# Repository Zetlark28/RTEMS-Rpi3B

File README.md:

# RTEMS-Rpi3B
Hi,

this repository is used for my thesis on RTEMS with rpi 3B+.

there are 4 directory:
- Notes : notes, sketch for thesis and project
- Guide : guide to install RTEMS on Host computer and create the first program
- Thesis : all files for my thesis
- SW : all source code of RTEMS
- HW : kicad
- Documents : all documents of RTEMS, rpi, kicad ecc.

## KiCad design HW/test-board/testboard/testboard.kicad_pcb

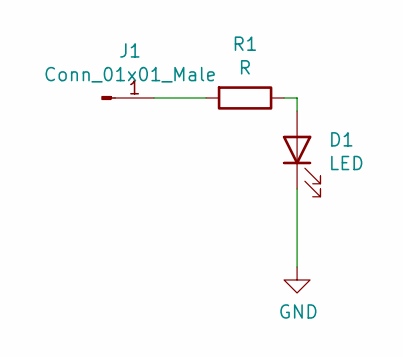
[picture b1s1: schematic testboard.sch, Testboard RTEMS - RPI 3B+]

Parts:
D1: LED; LED_D5.0mm
J1: Conn_01x01_Male; SolderWire-2sqmm_1x01_D2mm_OD3.9mm_Relief2x
R1: R; R_Axial_DIN0204_L3.6mm_D1.6mm_P2.54mm_Vertical

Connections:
GND: D1.1 (K)
unnamed: D1.2 (A), R1.1
unnamed: J1.1, R1.2

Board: 2 copper layers, 3 parts (0 on the bottom side), 2 nets, no tracks yet.

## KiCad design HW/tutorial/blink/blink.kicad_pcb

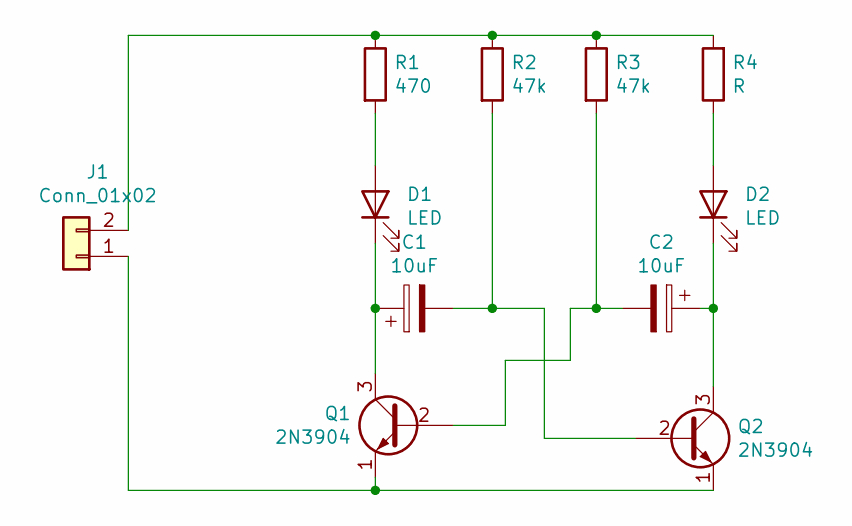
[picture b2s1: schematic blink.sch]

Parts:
C1, C2: 10uF; CP_Radial_D10.0mm_P5.00mm
D1, D2: LED; LED_D5.0mm
J1: Conn_01x02; PinHeader_1x02_P2.54mm_Horizontal
Q1, Q2: 2N3904; TO-92_Wide
R1: 470; R_Axial_DIN0516_L15.5mm_D5.0mm_P20.32mm_Horizontal
R2, R3: 47k; R_Axial_DIN0516_L15.5mm_D5.0mm_P20.32mm_Horizontal
R4: R; R_Axial_DIN0516_L15.5mm_D5.0mm_P20.32mm_Horizontal

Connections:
unnamed: C1.1, D1.1 (K), Q1.3 (C)
unnamed: C1.2, Q2.2 (B), R2.2
unnamed: C2.1, D2.1 (K), Q2.3 (C)
unnamed: C2.2, Q1.2 (B), R3.2
unnamed: D1.2 (A), R1.2
unnamed: D2.2 (A), R4.1
unnamed: J1.1, Q1.1 (E), Q2.1 (E)
unnamed: J1.2, R1.1, R2.1, R3.1, R4.2

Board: 2 copper layers, 11 parts (0 on the bottom side), 8 nets, no tracks yet.

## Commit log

2020-10-20 modified README
2020-10-20 added Notes and Documents directory
2020-10-20 added SW directory and hello-rpi programm
2020-10-20 added README
2020-10-22 added code sample from RTEMS src
2020-10-24 add led-test program
2020-10-25 added led-on and led-test source code
2020-10-25 added right datasheet document for RPI 3B+
2020-10-25 edited led-on sources file
2020-10-25 modified note
2020-10-25 deleted project
2020-10-25 added KICAD project
2020-10-26 added samples from git
2020-10-26 edited file
2020-10-26 added led-blink and edit files
2020-10-27 added fix led-blink
2020-10-28 fixed led-on and led-blink, added led.h library
2020-10-28 add datasheet rpi
2020-10-29 edited notes and added led-api-test
2020-10-30 fix led-api-rtems-tes
2020-11-02 edited main.c in led-api-rtems-test and bozze per la tesi
2020-11-02 created led-blink-more-in-0
2020-11-03 fixed led-blink-more, to refactor
2020-11-03 edited bozza tesi
2020-11-04 added bozza_guida_porting_rtems_rpi
2020-11-05 edited bozza_guida..
2020-11-06 added latex text guide porting
2020-11-08 added note from meeting
2020-11-09 edited led-blink-more structure
2020-11-09 added button project
2020-11-10 modified, not working
2020-11-10 polling button fix
2020-11-11 button-interrupt-test modified
2020-11-11 added firmware rpi compatible
2020-11-20 modified TODO
2020-11-20 added images to insert into the guide
2020-11-20 added correzioni da fare
2020-11-22 added todo
2020-11-22 edited guida porting and added images, need a revision
2020-11-27 edited bozza, added Microchip Maestro files
2020-12-01 added appunti fabrizio
2020-12-01 added datasheet
2020-12-07 added new file in microchip maestro folder
2020-12-15 added documentation
2020-12-16 added bozza introduzione
2020-12-20 edited prefazione, fixed introduzione bozza
2020-12-26 added data sheets
2020-12-26 edited introduzione
2021-01-10 modified thesis
2021-01-11 modified Tesi.tex
2021-01-12 added images
2021-01-13 add images
2021-01-14 edited tesi.tex
2021-01-21 add new version relazioine
2021-02-10 relaione 09 02 2021
2021-02-13 fine relazione
2021-02-14 aggiunta presentazione
2021-02-16 modificata presentazione
